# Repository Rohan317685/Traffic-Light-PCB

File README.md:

# traffic Light PCB

This is a PCB that's meant to mimic a traffic light! I made it because I thought it was cool and I wanted to learn more about timing and RC circuits!

Please keep in mind you need around 1% precise capacitors, resistors etc for exact accurate timing but normal parts do just fine: it may be off my 200-300 Milliseconds!

It uses RC timing and 2 Ne555p chip's that use Astable mode, this causes the led's to switch on and of just like a traffic light!

---
## Schematic

## PCB

---

This is for #resolution-hardware in hackclub which you should definitely join! :D

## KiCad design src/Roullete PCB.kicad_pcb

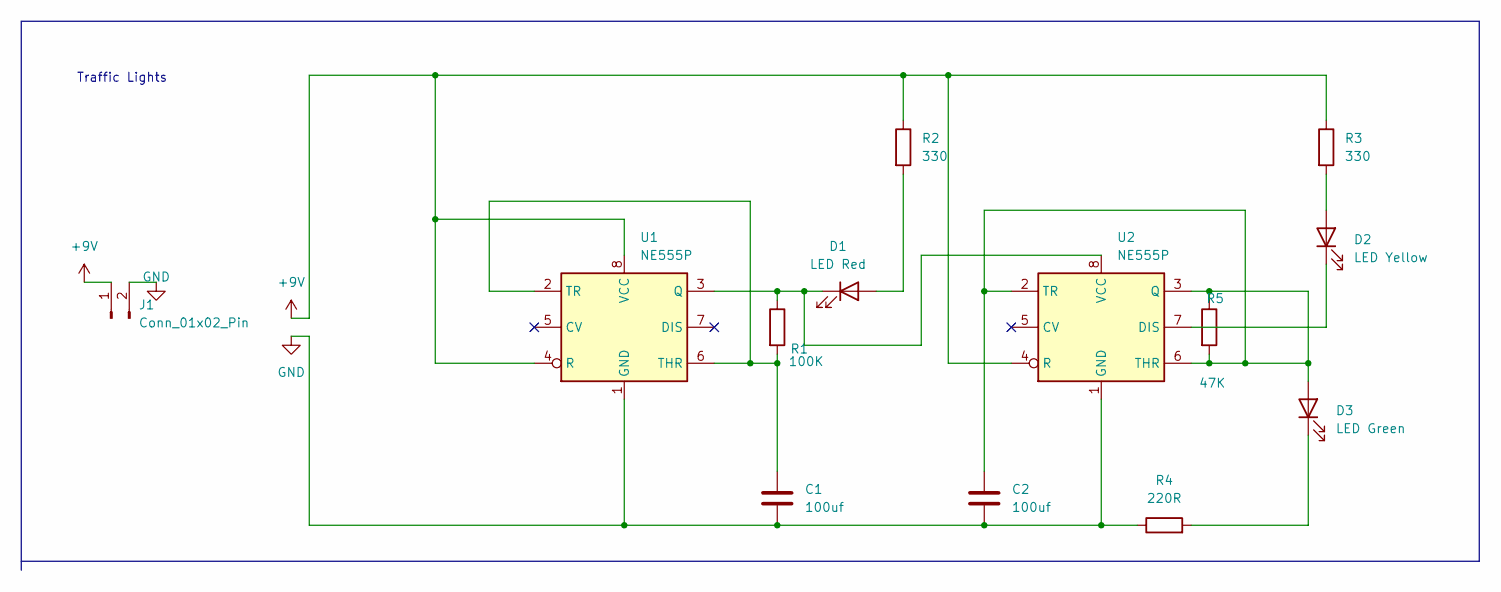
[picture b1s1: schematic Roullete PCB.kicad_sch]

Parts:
C1, C2: 100uf; CP_Radial_D5.0mm_P2.00mm
D1: LED Red; LED_D5.0mm
D2: LED Yellow; LED_D5.0mm
D3: LED Green; LED_D5.0mm
J1: Conn_01x02_Pin; PinHeader_1x02_P2.54mm_Vertical
R1: 100K; R_Axial_DIN0207_L6.3mm_D2.5mm_P10.16mm_Horizontal
R2, R3: 330; R_Axial_DIN0207_L6.3mm_D2.5mm_P10.16mm_Horizontal
R4: 220R; R_Axial_DIN0207_L6.3mm_D2.5mm_P10.16mm_Horizontal
R5: 47K; R_Axial_DIN0207_L6.3mm_D2.5mm_P10.16mm_Horizontal
U1, U2: NE555P; DIP-8_W7.62mm

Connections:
+9V: J1.1, R2.1, R3.1, U1.4 (R), U1.8 (VCC), U2.4 (R)
GND: C1.2, C2.2, J1.2, R4.1, U1.1 (GND), U2.1 (GND)
unnamed: D1.2 (A), R2.2
unnamed: D1.1 (K), R1.1, U1.3 (Q), U2.8 (VCC)
unnamed: D2.2 (A), R3.2
unnamed: D2.1 (K), U2.7 (DIS)
unnamed: C2.1, D3.2 (A), R5.1, R5.2, U2.2 (TR), U2.3 (Q), U2.6 (THR)
unnamed: D3.1 (K), R4.2
unnamed: C1.1, R1.2, U1.2 (TR), U1.6 (THR)

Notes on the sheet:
Traffic Lights

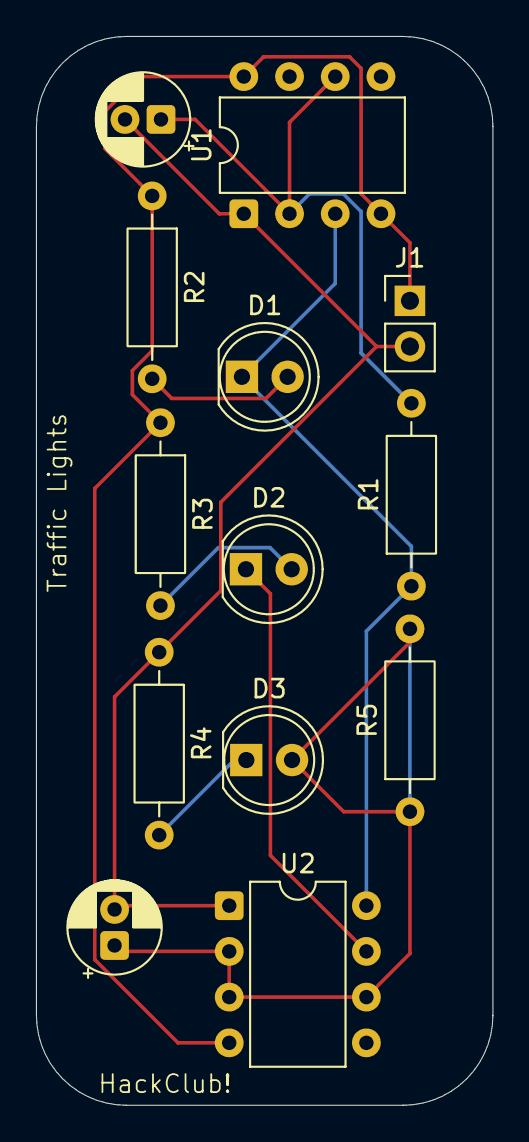
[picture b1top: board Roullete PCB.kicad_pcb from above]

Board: 2 copper layers, 25.4 x 59.4 mm, 13 parts (0 on the bottom side), 9 nets.

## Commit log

2026-04-04 Create placeholder
